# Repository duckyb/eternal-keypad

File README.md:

#  ETERNAL Keypad

<div class="shields">

</div>

### Sponsors

<span class="sponsors">

</span>
<div><sub>By purchasing from PCBWay I receive a percentage of the transaction</sub></div>

## Scope of the project

Eternal Keypad is an **open-source input device for gaming** that can be assembled for **both right and left hand mouse users**.

Historically there has been a scarcity of input devices for people that use their keyboard with their right hand and the mouse with the left, forcing some people to place their right hand in uncomfortable positions and/or requiring heavy remapping of in-game controls.
This device aims to fill this gap in the market that companies don't care about because the target is too small to turn a profit.

The device is Pro-micro compatible, so it's easier to build and source components.

## Features

⭕ Standard layout in a half-size form factor (all your keys are still there!)  
⭕ Ortholinear/grid layout for additional comfort  
⭕ Bluetooth support (nice!nano, battery, ZMK, power switch)  
⭕ Hotswap with Kailh Sockets  
⭕ RGB Underglow  
⭕ 3 macro buttons  
⭕ Easy to build  
⭕ Files for FR4 or laser cut plate case included  

## How can I make this?

### Components list (latest PCB version)

#### For the Keyboard (required)

- 1× [ETERNAL Keypad PCB](https://github.com/duckyb/eternal-keypad/releases/latest)
- 36× through-hole or surface-mount diodes. (I use "1N4148 CDIL" from tme.eu)
- 36× MX style switches
- 36× Kailh Hotswap Sockets
- 1× Stabilizer (2u)
- 36× Keycaps (The set pictured above is "Honey & Milk XDA")
- 1× Microcontroller (Pro-micro or equivalent)

Optionals:
- 8× WS2812B RGB LEDs
- 1× Slider switch (for wireless)
- 1× LiPo battery (type: 301230, for wireless)

#### For the case (recommended)

- 1× [ETERNAL Keypad switch plate & bottom plate](https://github.com/duckyb/eternal-keypad/releases/latest)
  - If you want to have underglow RGB you should order a laser-cut bottom plate from acrylic, using the included `.dxf` file. If you don't care about underglow you can get an FR4 bottom plate PCB using the gerber file.
- 8× M2 Screws (I use "1154095 BOSSARD" from tme.eu)
- 4× M2 standoffs (diameter: 3mm, length: 8mm)
- 4× Rubber bump-on feet

### Buy as a DIY Kit

It might be more convenient to purchase this project as a kit, check out the [vendors page](./vendors.md).

## FAQ

Check the [dedicated page](./FAQ.md)

## Firmware

You can find firmwares in the [release section](https://github.com/duckyb/eternal-keypad/releases/latest), ready to download and flash.
If you want to customize them, you can do so using QMK, ZMK or VIA.

Note:
- The "A" and "D" keys are not mirrored to avoid inverting movement controls with default key-bindings.
- The "FN" key is used to access the missing half of the keyboard
- Holding the 0 key turns WASD into arrow keys

## Additional Resources

- 3D Printed case by chewiedies → [v4](https://www.thingiverse.com/thing:5329104), [v5, and v6](https://www.printables.com/model/290027-eternal-keypad-v12-gasket-mount-case-w-optional-te)

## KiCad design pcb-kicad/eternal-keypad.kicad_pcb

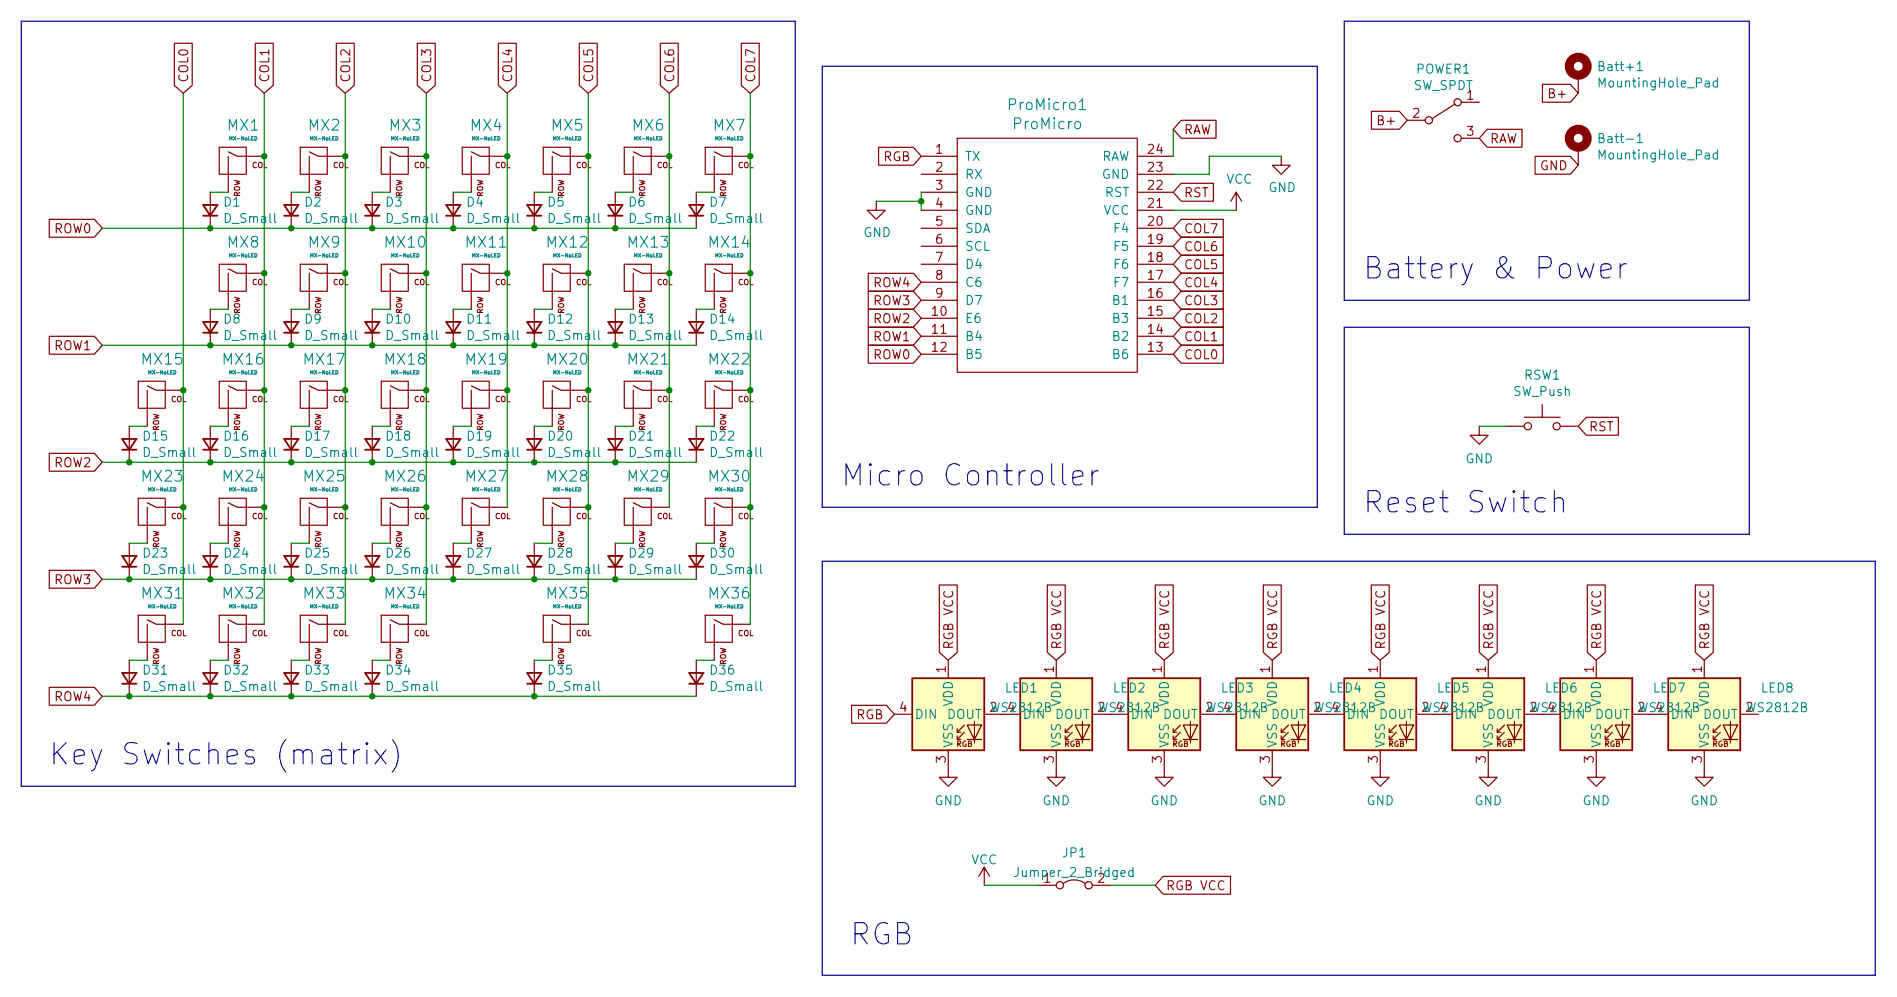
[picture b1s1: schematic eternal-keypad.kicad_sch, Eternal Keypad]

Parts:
Batt+1: MountingHole_Pad; 1pin_conn
Batt-1: MountingHole_Pad; 1pin_conn
D1, D2, D3, D4, D5, D6, D7, D8, D9, D10, D11, D12, D13, D14, D15, D16, D17, D18, D19, D20, D21, D22, D23, D24, D25, D26, D27, D28, D29, D30, D31, D32, D33, D34, D35, D36: D_Small; D_DO-35_SOD27_P7.62mm_Horizontal_Reversible
JP1: Jumper_2_Bridged; SolderJumper-2_P1.3mm_Bridged2Bar_RoundedPad1.0x1.5mm
LED1, LED2, LED3, LED4, LED5, LED6, LED7, LED8: WS2812B; LED_WS2812B_PLCC4_5.0x5.0mm_P3.2mm
MX1, MX8, MX16, MX24, MX32: MX-NoLED; MXOnly-1.25U-Reversible-NoLED
MX2, MX3, MX4, MX5, MX6, MX7, MX9, MX10, MX11, MX12, MX13, MX14, MX15, MX17, MX18, MX19, MX20, MX21, MX22, MX23, MX25, MX26, MX27, MX28, MX29, MX30, MX31, MX33, MX34, MX36: MX-NoLED; MXOnly-1U-Reversible-NoLED
MX35: MX-NoLED; MXOnly-3U-Reversible-ReversedStabilizers-NoLED
POWER1: SW_SPDT; SPDT_C128955
ProMicro1: ProMicro
RSW1: SW_Push; Tactile-Switch_SMT

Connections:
B+: Batt+1.1, POWER1.2 (B)
COL0: MX15.1 (COL), MX23.1 (COL), MX31.1 (COL), ProMicro1.13 (B6)
COL1: MX1.1 (COL), MX8.1 (COL), MX16.1 (COL), MX24.1 (COL), MX32.1 (COL), ProMicro1.14 (B2)
COL2: MX2.1 (COL), MX9.1 (COL), MX17.1 (COL), MX25.1 (COL), MX33.1 (COL), ProMicro1.15 (B3)
COL3: MX3.1 (COL), MX10.1 (COL), MX18.1 (COL), MX26.1 (COL), MX34.1 (COL), ProMicro1.16 (B1)
COL4: MX4.1 (COL), MX11.1 (COL), MX19.1 (COL), MX27.1 (COL), ProMicro1.17 (F7)
COL5: MX5.1 (COL), MX12.1 (COL), MX20.1 (COL), MX28.1 (COL), MX35.1 (COL), ProMicro1.18 (F6)
COL6: MX6.1 (COL), MX13.1 (COL), MX21.1 (COL), MX29.1 (COL), ProMicro1.19 (F5)
COL7: MX7.1 (COL), MX14.1 (COL), MX22.1 (COL), MX30.1 (COL), MX36.1 (COL), ProMicro1.20 (F4)
GND: Batt-1.1, LED1.3 (VSS), LED2.3 (VSS), LED3.3 (VSS), LED4.3 (VSS), LED5.3 (VSS), LED6.3 (VSS), LED7.3 (VSS), LED8.3 (VSS), ProMicro1.3 (GND), ProMicro1.4 (GND), ProMicro1.23 (GND), RSW1.1
unnamed: D1.2 (A), MX1.2 (ROW)
unnamed: D2.2 (A), MX2.2 (ROW)
unnamed: D3.2 (A), MX3.2 (ROW)
unnamed: D4.2 (A), MX4.2 (ROW)
unnamed: D5.2 (A), MX5.2 (ROW)
unnamed: D6.2 (A), MX6.2 (ROW)
unnamed: D7.2 (A), MX7.2 (ROW)
unnamed: D8.2 (A), MX8.2 (ROW)
unnamed: D9.2 (A), MX9.2 (ROW)
unnamed: D10.2 (A), MX10.2 (ROW)
unnamed: D11.2 (A), MX11.2 (ROW)
unnamed: D12.2 (A), MX12.2 (ROW)
unnamed: D13.2 (A), MX13.2 (ROW)
unnamed: D14.2 (A), MX14.2 (ROW)
unnamed: D15.2 (A), MX15.2 (ROW)
unnamed: D16.2 (A), MX16.2 (ROW)
unnamed: D17.2 (A), MX17.2 (ROW)
unnamed: D18.2 (A), MX18.2 (ROW)
unnamed: D19.2 (A), MX19.2 (ROW)
unnamed: D20.2 (A), MX20.2 (ROW)
unnamed: D21.2 (A), MX21.2 (ROW)
unnamed: D22.2 (A), MX22.2 (ROW)
unnamed: D23.2 (A), MX23.2 (ROW)
unnamed: D24.2 (A), MX24.2 (ROW)
unnamed: D25.2 (A), MX25.2 (ROW)
unnamed: D26.2 (A), MX26.2 (ROW)
unnamed: D27.2 (A), MX27.2 (ROW)
unnamed: D28.2 (A), MX28.2 (ROW)
unnamed: D29.2 (A), MX29.2 (ROW)
unnamed: D30.2 (A), MX30.2 (ROW)
unnamed: D31.2 (A), MX31.2 (ROW)
unnamed: D32.2 (A), MX32.2 (ROW)
unnamed: D33.2 (A), MX33.2 (ROW)
unnamed: D34.2 (A), MX34.2 (ROW)
unnamed: D35.2 (A), MX35.2 (ROW)
unnamed: D36.2 (A), MX36.2 (ROW)
unnamed: LED1.2 (DOUT), LED2.4 (DIN)
unnamed: LED2.2 (DOUT), LED3.4 (DIN)
unnamed: LED3.2 (DOUT), LED4.4 (DIN)
unnamed: LED4.2 (DOUT), LED5.4 (DIN)
unnamed: LED5.2 (DOUT), LED6.4 (DIN)
unnamed: LED6.2 (DOUT), LED7.4 (DIN)
unnamed: LED7.2 (DOUT), LED8.4 (DIN)
RAW: POWER1.3 (C), ProMicro1.24 (RAW)
RGB: LED1.4 (DIN), ProMicro1.1 (TX)
RGB VCC: JP1.2 (B), LED1.1 (VDD), LED2.1 (VDD), LED3.1 (VDD), LED4.1 (VDD), LED5.1 (VDD), LED6.1 (VDD), LED7.1 (VDD), LED8.1 (VDD)
ROW0: D1.1 (K), D2.1 (K), D3.1 (K), D4.1 (K), D5.1 (K), D6.1 (K), D7.1 (K), ProMicro1.12 (B5)
ROW1: D8.1 (K), D9.1 (K), D10.1 (K), D11.1 (K), D12.1 (K), D13.1 (K), D14.1 (K), ProMicro1.11 (B4)
ROW2: D15.1 (K), D16.1 (K), D17.1 (K), D18.1 (K), D19.1 (K), D20.1 (K), D21.1 (K), D22.1 (K), ProMicro1.10 (E6)
ROW3: D23.1 (K), D24.1 (K), D25.1 (K), D26.1 (K), D27.1 (K), D28.1 (K), D29.1 (K), D30.1 (K), ProMicro1.9 (D7)
ROW4: D31.1 (K), D32.1 (K), D33.1 (K), D34.1 (K), D35.1 (K), D36.1 (K), ProMicro1.8 (C6)
RST: ProMicro1.22 (RST), RSW1.2
VCC: JP1.1 (A), ProMicro1.21 (VCC)

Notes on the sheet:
Reset Switch
RGB
Battery & Power
Key Switches (matrix)
Micro Controller

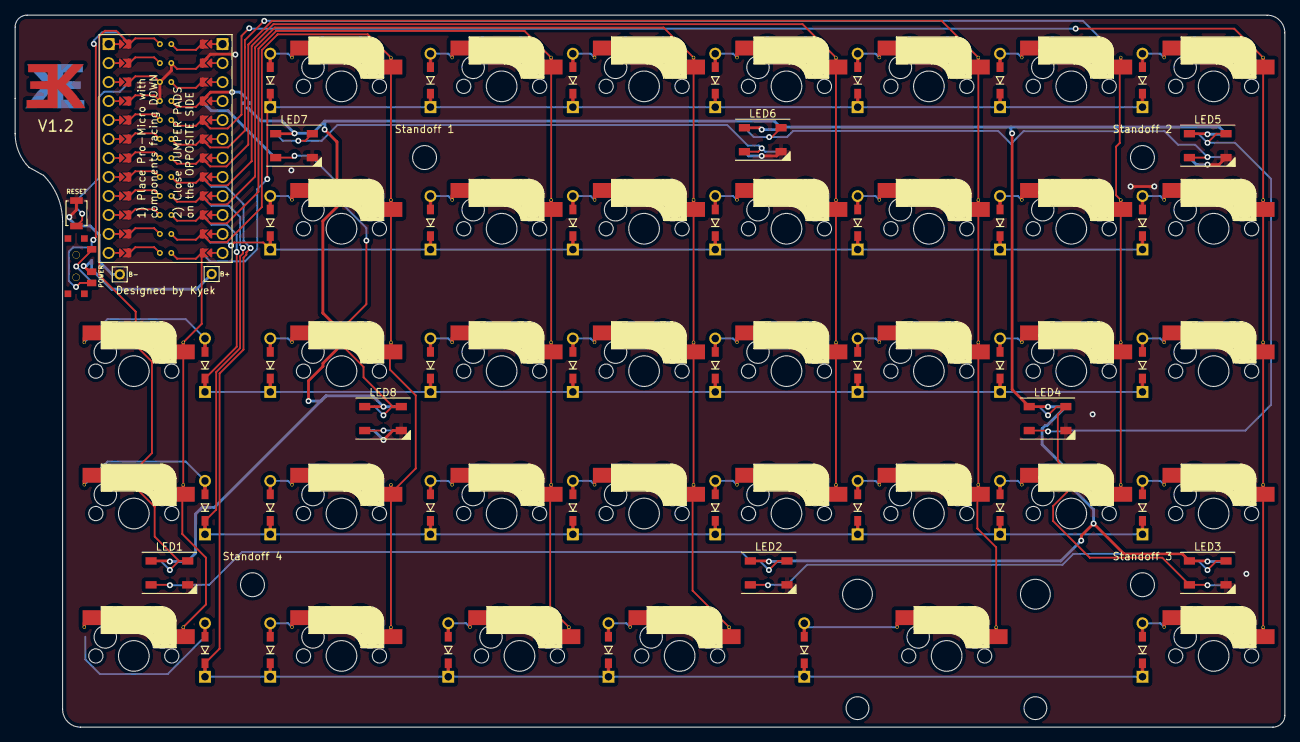
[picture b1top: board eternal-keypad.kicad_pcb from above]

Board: 2 copper layers, 169.9 x 95.2 mm, 91 parts (1 on the bottom side), 63 nets.

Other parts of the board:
STAB1: Stabilizer_MX_2u
Standoff 1, Standoff 2, Standoff 3, Standoff 4: MountingHole_4.6mm_Pad_Via; MountingHole_3.2mm_M3_DIN965

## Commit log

2021-10-13 Create project
2021-10-13 Add library submodules
2021-10-13 Add libraries to project
2021-10-13 Test schematic ready
2021-10-13 Add ProMicro submodule
2021-10-13 Add ProMicro footprints
2021-10-14 Non flippable version test
2021-10-14 Update README with project scope
2021-10-14 Fresh start
2021-10-14 Update silkscreen
2021-10-15 Front silk screen
2021-10-15 Rename project to Eternal Keypad
2021-10-15 Add ƎK logo
2021-10-15 Update project scope and add schedule
2021-10-15 Correction in readme
2021-10-15 Add layouts table
2021-10-16 First prototype ready
2021-10-17 Update PCB and add firmware
2021-10-17 Update preview and fill zone
2021-10-28 Add keypad picture preview and update schedule
2021-11-14 Add plates and bump version
2021-11-14 Final adjustments and case patterns
2021-11-14 Remove unused footprints
2021-11-14 Rearrange repository files
2021-12-05 Update firmware preview
2021-12-09 Add youtube guide link
2021-12-11 Add badges
2021-12-11 Upgrade logo to svg
2021-12-12 Add logo alt text for SEO
2021-12-12 Create LICENSE
2021-12-16 Add FAQ and license shield
2022-05-06 Add discord invite
2022-05-11 Update preview image
2022-05-11 Add via support badge with link
2022-05-12 Enable Discord badge w/ invite
2022-05-13 Publish v1.1
2022-05-13 Remove recommended standoffs from README
2022-05-14 Add power, reset, RGB Cutoff, Battery Pads
2022-05-17 Add release and build workflows
2022-05-17 Update plates to Kicadv6
2022-05-17 Update board constraints
2022-05-20 Update component list
2022-05-22 Add 3D models
2022-09-02 Add vendor
2022-09-03 Add KEEBD to Vendors
2022-09-03 Removed version
2022-09-05 Add ZMK badge and feature list
2022-09-17 Add Beekeeb vendor
2022-09-17 Update pricings
2022-09-24 Add sponsors sections
2022-09-24 Add sponsor url
2022-09-30 Add PMM sponsor
2022-11-10 Add PCBWay sponsor
2023-09-12 docs: improve formatting
2023-09-13 docs: add v6 version of the case
